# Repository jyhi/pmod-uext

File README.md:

<!--
    SPDX-FileCopyrightText: 2025 Junde Yhi <junde@yhi.moe>
    SPDX-License-Identifier: CC-BY-SA-4.0
-->

# Pmod&trade; Compatible UEXT Adapter Board

This Digilent Pmod&trade; Compatible module converts between a 12-pin Pmod interface to an Olimex Universal Extension Connector (UEXT) interface.

## Errata 1.x

This section lists known issues of the product in version 1.x.

- It's difficult to solder VCC and GND pins.
    - Reason: too much thermal relief.
    - Mitigation: use flux and retain soldering tip on the plate for an extended time.
- SW1 switch positions doesn't match the description printed beside it.
    - Reason: on the PCB design file, SW1 is mistakenly placed upside-down.
    - Mitigation: flip SW1 by 180 degree, replacing it upright (i.e. first pin at the bottom-left corner). This doesn't change the function of the DIP switch.
- I2C pins (under Pmod Type 6/A) cross-talk with each other slightly (approximately 100mV).
    - Reason: suboptimal PCB trace placement.
    - Mitigation: none. In theory, the cross-talk signal won't be strong enough to disrupt the signals on another pin.

## Use

Select a Pmod interface type with the DIP switch (SW1). This routes the correct pins between Pmod and UEXT.

| Left | Right | Pmod Interface  |
| ---- | ----- | --------------- |
| Off  | Off   | Type 1A (GPIO)  |
| Off  | On    | Type 2A (SPI)   |
| On   | Off   | Type 3A (UART)  |
| On   | On    | Type 6A (I2C)   |

Power and ground on both sides are always connected. Other I/O pins are left open. Note that the module is not completely passive: the onboard multiplexers take power. If a voltage supply is higher than 5V, they can be destroyed. Most (if not all) Pmod and UEXT modules run on 3.3V. This module should only be used in compliant Pmod and UEXT systems.

### Type 1A (GPIO) Mappings

| Pmod Pin     | UEXT Pin  |
| ------------ | --------- |
|  1 (GPIO  1) |  3 (TXD)  |
|  2 (GPIO  2) |  4 (RXD)  |
|  3 (GPIO  3) |  5 (SCL)  |
|  4 (GPIO  4) |  6 (SDA)  |
|  7 (GPIO  7) |  7 (MISO) |
|  8 (GPIO  8) |  8 (MOSI) |
|  9 (GPIO  9) |  9 (SCK)  |
| 10 (GPIO 10) | 10 (SSEL) |

### Type 2A (SPI) Mappings

| Pmod Pin | UEXT Pin  |
| -------- | --------- |
| 1 (CS)   | 10 (SSEL) |
| 2 (MOSI) |  8 (MOSI) |
| 3 (MISO) |  7 (MISO) |
| 4 (SCK)  |  9 (SCK)  |

### Type 3A (UART) Mappings

| Pmod Pin | UEXT Pin  |
| -------- | --------- |
| 2 (TXD)  | 3 (TXD)   |
| 3 (RXD)  | 4 (RXD)   |

### Type 6A (I2C) Mappings

| Pmod Pin | UEXT Pin  |
| -------- | --------- |
| 3 (SCL)  | 3 (SCL)   |
| 4 (SDA)  | 4 (SDA)   |

## License

The hardware design is licensed under the [CERN Open Hardware Licence Version 2 (Strongly Reciprocal)][ohl-s-2.0]. A copy of license text can be found at [LICENSES/CERN-OHL-S-2.0.txt](./LICENSES/CERN-OHL-S-2.0.txt).

Non-hardware contents in this project are licensed under the [Creative Commons Attribution-ShareAlike 4.0 International][cc-by-sa-4.0] license. A copy of license text can be found at [LICENSES/CC-BY-SA-4.0.txt](./LICENSES/CC-BY-SA-4.0.txt).

Check [REUSE.toml](./REUSE.toml) for information about licenses applicable to individual files. Alternatively, check the comment header of a file for the license applicable to it. For details, visit <https://reuse.software>.

[ohl-s-2.0]: https://ohwr.org/cern_ohl_s_v2.pdf
[cc-by-sa-4.0]: https://creativecommons.org/licenses/by-sa/4.0/

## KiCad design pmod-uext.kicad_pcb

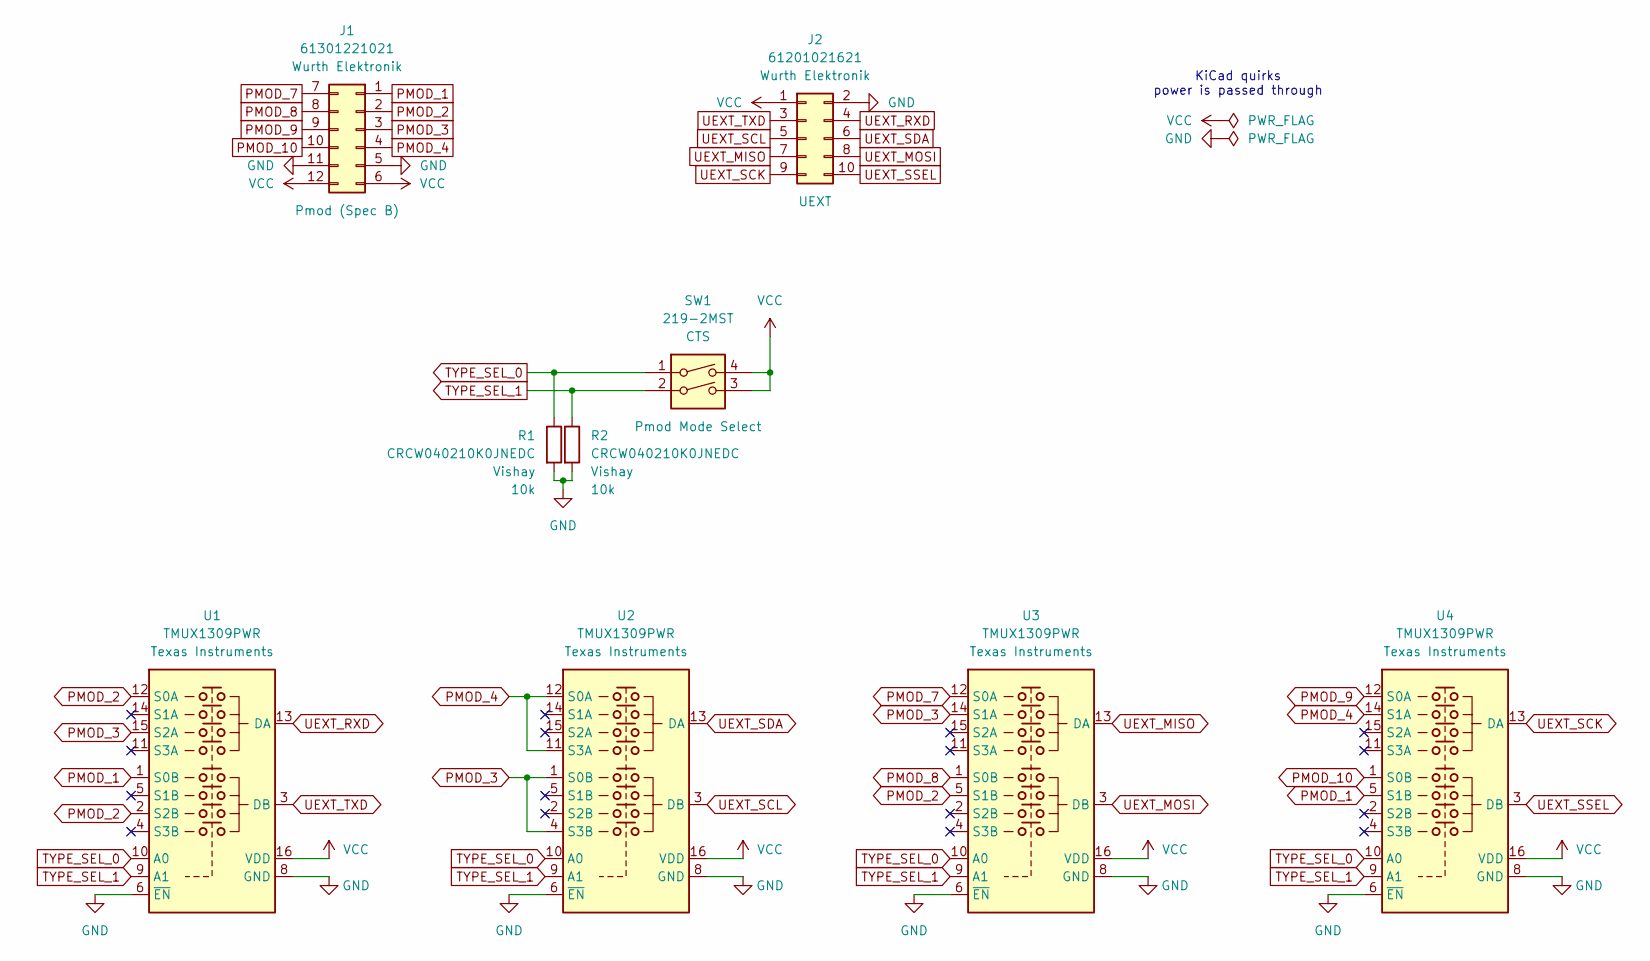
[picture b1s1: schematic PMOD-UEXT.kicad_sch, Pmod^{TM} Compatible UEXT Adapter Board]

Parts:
J1: 61301221021; PinHeader_2x06_P2.54mm_Horizontal
J2: 61201021621; IDC-Header_2x05_P2.54mm_Vertical
R1, R2: CRCW040210K0JNEDC; R_0402_1005Metric_Pad0.72x0.64mm_HandSolder
SW1: 219-2MST; SW_DIP_SPSTx02_Slide_6.7x6.64mm_W8.61mm_P2.54mm_LowProfile
U1, U2, U3, U4: TMUX1309PWR; TSSOP-16_4.4x5mm_P0.65mm

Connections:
GND: J1.5, J1.11, J2.2, R1.2, R2.2, U1.6 (~EN), U1.8 (GND), U2.6 (~EN), U2.8 (GND), U3.6 (~EN), U3.8 (GND), U4.6 (~EN), U4.8 (GND)
PMOD_1: J1.1, U1.1 (S0B), U4.5 (S1B)
PMOD_2: J1.2, U1.2 (S2B), U1.12 (S0A), U3.5 (S1B)
PMOD_3: J1.3, U1.15 (S2A), U2.1 (S0B), U2.4 (S3B), U3.14 (S1A)
PMOD_4: J1.4, U2.11 (S3A), U2.12 (S0A), U4.14 (S1A)
PMOD_7: J1.7, U3.12 (S0A)
PMOD_8: J1.8, U3.1 (S0B)
PMOD_9: J1.9, U4.12 (S0A)
PMOD_10: J1.10, U4.1 (S0B)
TYPE_SEL_0: R1.1, SW1.1, U1.10 (A0), U2.10 (A0), U3.10 (A0), U4.10 (A0)
TYPE_SEL_1: R2.1, SW1.2, U1.9 (A1), U2.9 (A1), U3.9 (A1), U4.9 (A1)
UEXT_MISO: J2.7, U3.13 (DA)
UEXT_MOSI: J2.8, U3.3 (DB)
UEXT_RXD: J2.4, U1.13 (DA)
UEXT_SCK: J2.9, U4.13 (DA)
UEXT_SCL: J2.5, U2.3 (DB)
UEXT_SDA: J2.6, U2.13 (DA)
UEXT_SSEL: J2.10, U4.3 (DB)
UEXT_TXD: J2.3, U1.3 (DB)
VCC: J1.6, J1.12, J2.1, SW1.3, SW1.4, U1.16 (VDD), U2.16 (VDD), U3.16 (VDD), U4.16 (VDD)

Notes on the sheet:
KiCad quirks power is passed through

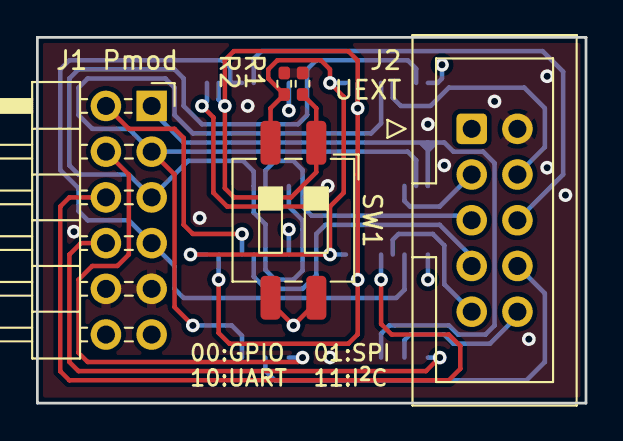
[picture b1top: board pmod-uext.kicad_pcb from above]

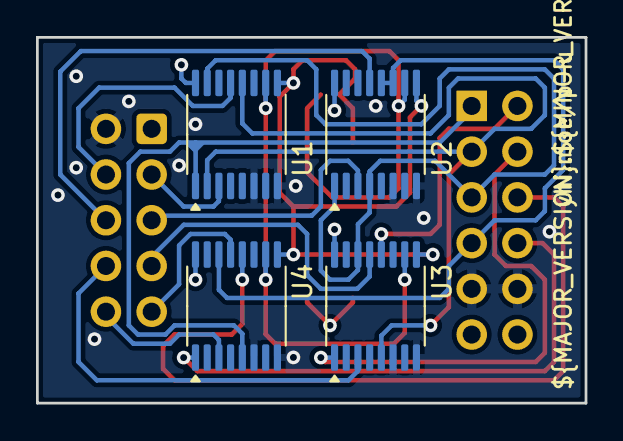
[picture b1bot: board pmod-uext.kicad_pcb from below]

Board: 4 copper layers, 30.5 x 20.3 mm, 9 parts (4 on the bottom side), 20 nets.

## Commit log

2025-04-01 add design source files
2025-04-01 add changelog
2025-04-01 change remembered plot options
2025-04-01 fix images in readme
2025-04-01 add major license at common location
2025-04-26 change project metas
    - rename files with more accurate names
    - remove unnecessary files
    - improve documents, also reflect structural changes
2025-04-26 add errata for 1.x

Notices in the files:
PMOD-UEXT.kicad_sch:
© 2025 Junde Yhi
SPDX-License-Identifier: CERN-OHL-S-2.0
